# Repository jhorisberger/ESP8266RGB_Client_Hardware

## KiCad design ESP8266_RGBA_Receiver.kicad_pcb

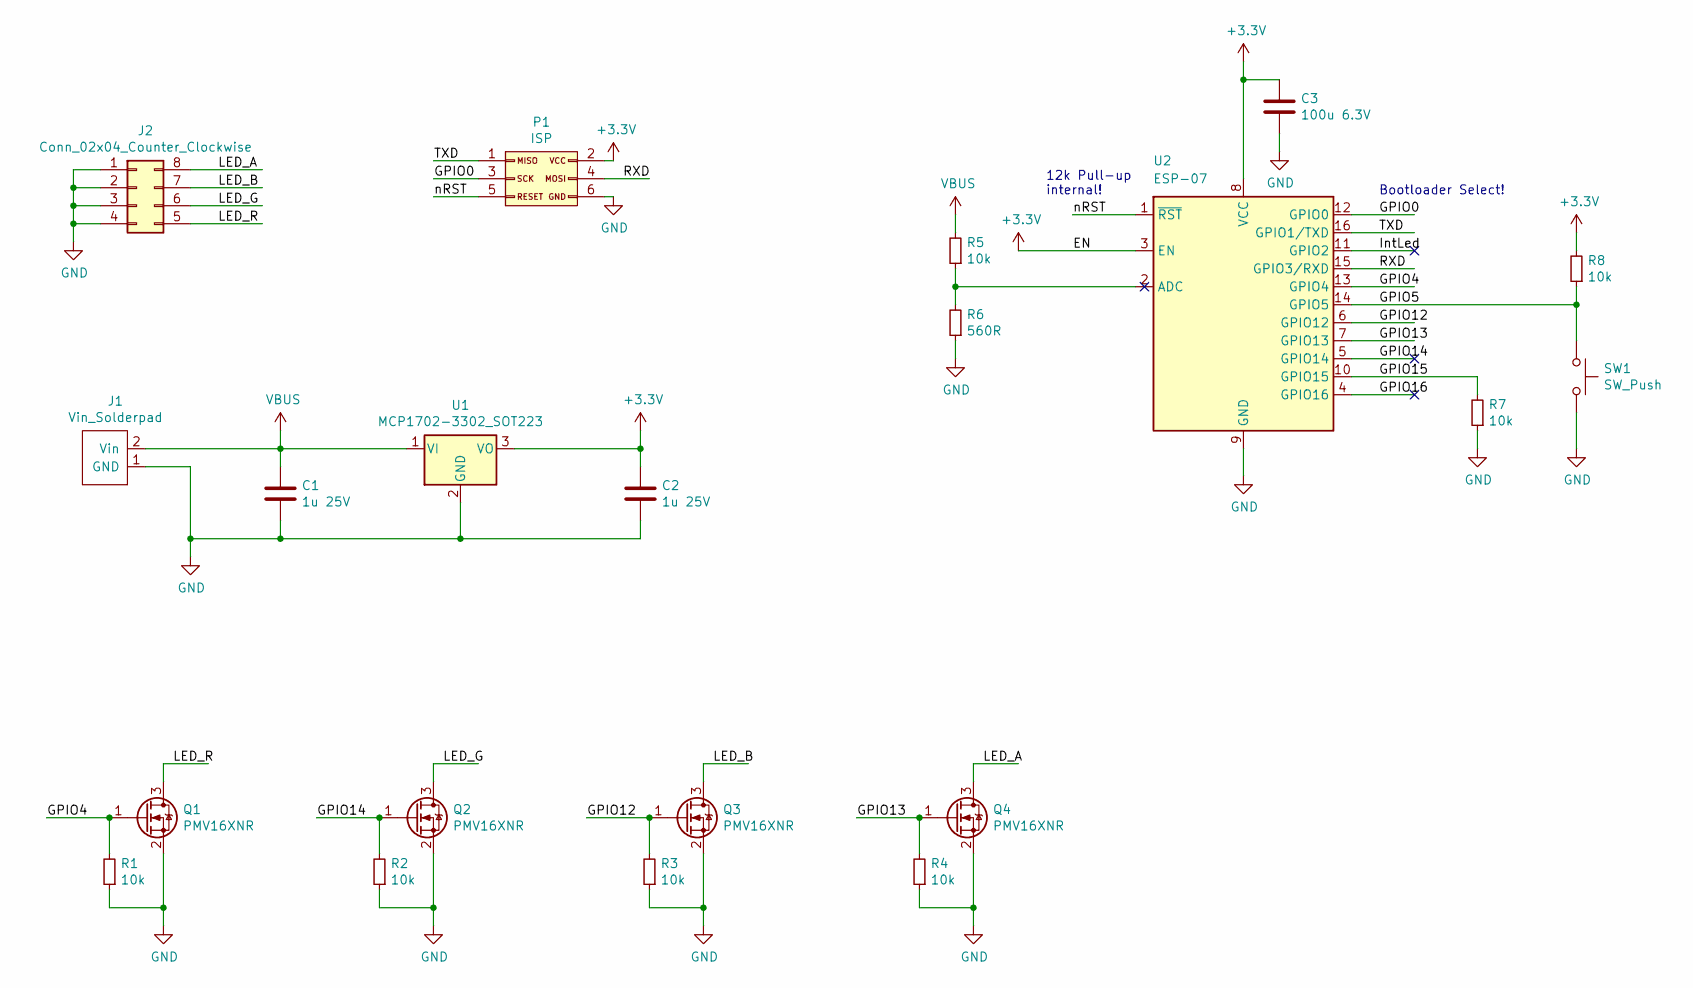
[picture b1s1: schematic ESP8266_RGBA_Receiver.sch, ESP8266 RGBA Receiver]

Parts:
C1, C2: 1u 25V; C_0603_1608Metric
C3: 100u 6.3V; C_1206_3216Metric
J1: Vin_Solderpad; 2Wire_Solder_large
J2: Conn_02x04_Counter_Clockwise; MolexMicroFit3.0_2x8_StradleMount
P1: ISP; POGO_ISP
Q1, Q2, Q3, Q4: PMV16XNR; SOT-23
R1, R2, R3, R4, R5, R7, R8: 10k; R_0603_1608Metric
R6: 560R; R_0603_1608Metric
SW1: SW_Push; SW_SPST_PTS810
U1: MCP1702-3302_SOT223; SOT-223-3_TabPin2
U2: ESP-07

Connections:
+3V3: C2.1, C3.1, P1.2, R8.2, U1.3 (VO), U2.3 (EN), U2.8 (VCC)
/GPIO0: P1.3, U2.12 (GPIO0)
/GPIO4: Q1.1 (G), R1.2, U2.13 (GPIO4)
/GPIO5: R8.1, SW1.1, U2.14 (GPIO5)
/GPIO12: Q3.1 (G), R3.2, U2.6 (GPIO12)
/GPIO13: Q4.1 (G), R4.2, U2.7 (GPIO13)
/GPIO14: Q2.1 (G), R2.2, U2.5 (GPIO14)
/GPIO15: R7.2, U2.10 (GPIO15)
/GPIO16: U2.4 (GPIO16)
/IntLed: U2.11 (GPIO2)
/LED_A: J2.8, Q4.3 (D)
/LED_B: J2.7, Q3.3 (D)
/LED_G: J2.6, Q2.3 (D)
/LED_R: J2.5, Q1.3 (D)
/RXD: P1.4, U2.15 (GPIO3/RXD)
/TXD: P1.1, U2.16 (GPIO1/TXD)
/nRST: P1.5, U2.1 (~RST)
GND: C1.2, C2.2, C3.2, J1.1 (GND), J2.1, J2.2, J2.3, J2.4, P1.6, Q1.2 (S), Q2.2 (S), Q3.2 (S), Q4.2 (S), R1.1, R2.1, R3.1, R4.1, R6.1, R7.1, SW1.2, U1.2 (GND), U2.9 (GND)
unnamed: R5.1, R6.2, U2.2 (ADC)
VBUS: C1.1, J1.2 (Vin), R5.2, U1.1 (VI)

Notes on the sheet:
12k Pull-up internal!
Bootloader Select!

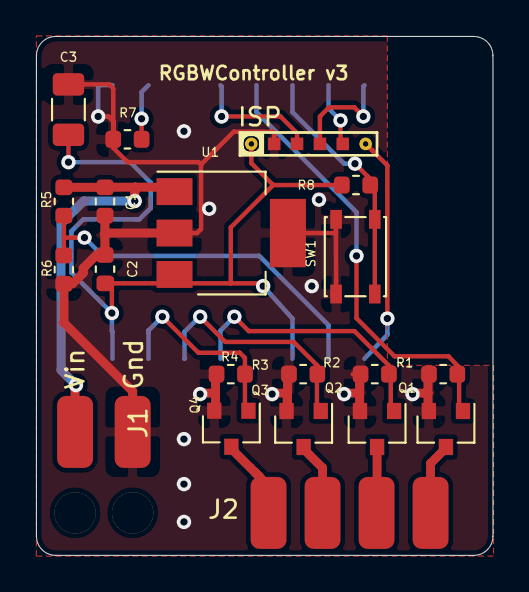
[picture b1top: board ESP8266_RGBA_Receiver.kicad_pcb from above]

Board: 2 copper layers, 25.4 x 28.8 mm, 21 parts (1 on the bottom side), 18 nets.

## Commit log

2020-11-11 Initial commit HW Version "v2" as ordered on PCBWay
2020-11-13 v3 as ordered on JLC PCB: ------------------------- - Replaced LED connector with Molex straddle mounted on the PCB - Moved button from GPIO0 to GPIO5 - Enlarged holes for powerinput
